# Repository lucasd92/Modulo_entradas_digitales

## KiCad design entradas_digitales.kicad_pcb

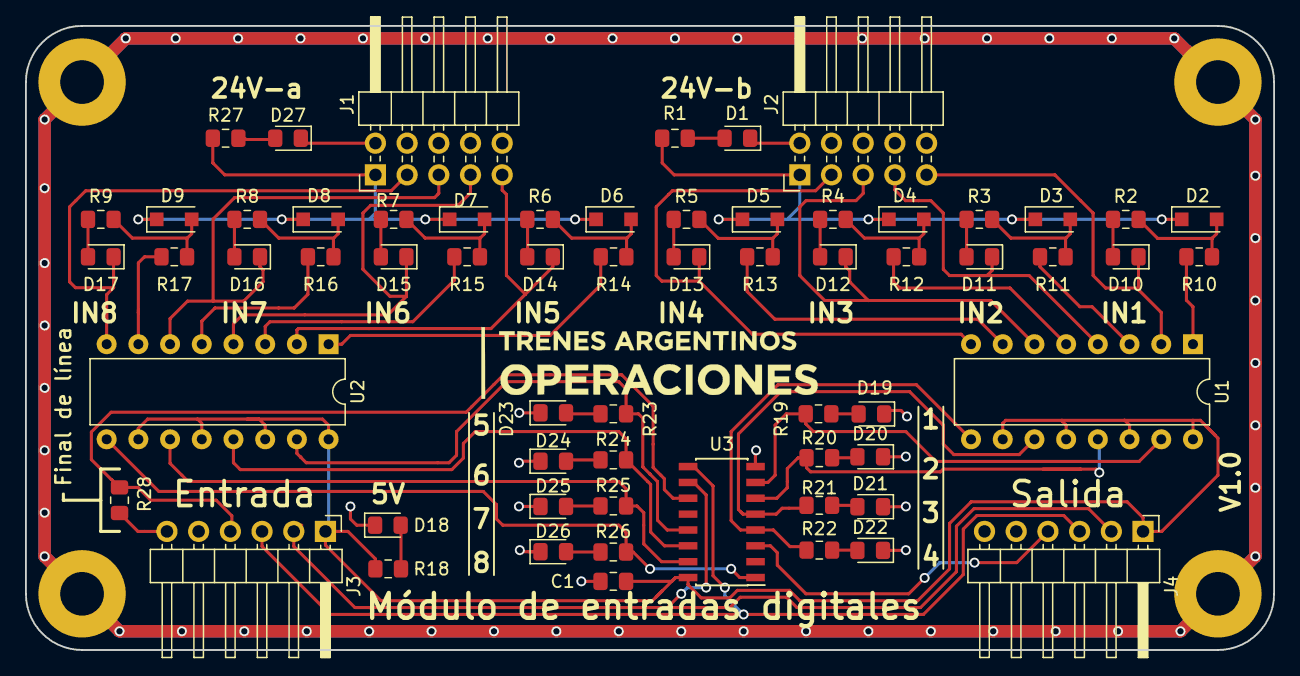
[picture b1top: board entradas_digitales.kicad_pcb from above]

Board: 2 copper layers, 100.0 x 50.0 mm, 68 parts (0 on the bottom side), 61 nets.

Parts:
C1: 100nF; C_0805_2012Metric_Pad1.15x1.40mm_HandSolder
D1, D10, D11, D12, D13, D14, D15, D16, D17, D18, D19, D20, D21, D22, D23, D24, D25, D26, D27: LED; LED_0805_2012Metric_Pad1.15x1.40mm_HandSolder
D2: KDZVTFTR12B; D_SOD-123F
D3, D4, D5, D6, D7, D8, D9: D_Zener; D_SOD-123F
G1: TrenesArgentinosLogo
J1: Opto5-8; PinHeader_2x05_P2.54mm_Horizontal
J2: Opto1-4; PinHeader_2x05_P2.54mm_Horizontal
J3: Entrada; PinHeader_1x06_P2.54mm_Horizontal
J4: Salida; PinHeader_1x06_P2.54mm_Horizontal
MH1, MH2, MH3, MH4: MountingHole_Pad; MountingHole_3.5mm_Pad
R1, R2, R3, R4, R5, R6, R7, R8, R9, R10, R11, R12, R13, R14, R15, R16, R17, R18, R19, R20, R21, R22, R23, R24, R25, R26, R27, R28: R; R_0805_2012Metric_Pad1.15x1.40mm_HandSolder
U1, U2: TLP627-4; DIP-16_W7.62mm
U3: 4021; SOIC-16_3.9x9.9mm_P1.27mm

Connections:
/1: R19.2, U1.15, U3.7
/2: R20.2, U1.13, U3.6
/3: R21.2, U1.11, U3.5
/4: R22.2, U1.9, U3.4
/5: R23.2, U2.15, U3.13
/6: R24.2, U2.13, U3.14
/7: R25.2, U2.11, U3.15
/8: R26.2, U2.9, U3.1
/24V-A: D2.1, D3.1, D4.1, D5.1, J2.1, R1.2
/24V-B: D6.1, D7.1, D8.1, D9.1, J1.1, R27.2
/CLK: J3.2, J4.2, U3.10
/GND-A: D1.1, J2.2
/GND-B: D27.1, J1.2
/IN1: D10.1, J2.9, U1.2
/IN2: D11.1, J2.7, U1.4
/IN3: D12.1, J2.5, U1.6
/IN4: D13.1, J2.3, U1.8
/IN5: D14.1, J1.9, U2.2
/IN6: D15.1, J1.7, U2.4
/IN7: D16.1, J1.5, U2.6
/IN8: D17.1, J1.3, U2.8
/PS: J3.3, J4.3, U3.9
/SIN: J3.4, R28.1, U3.11
/SOUT: J4.4, U3.3
unnamed: D1.2, R1.1
unnamed: D2.2, R2.1, R10.2
unnamed: D3.2, R3.1, R11.2
unnamed: D4.2, R4.1, R12.2
unnamed: D5.2, R5.1, R13.2
unnamed: D6.2, R6.1, R14.2
unnamed: D7.2, R7.1, R15.2
unnamed: D8.2, R8.1, R16.2
unnamed: D9.2, R9.1, R17.2
unnamed: D10.2, R2.2
unnamed: D11.2, R3.2
unnamed: D12.2, R4.2
unnamed: D13.2, R5.2
unnamed: D14.2, R6.2
unnamed: D15.2, R7.2
unnamed: D16.2, R8.2
unnamed: D17.2, R9.2
unnamed: D18.2, R18.1
unnamed: D19.2, R19.1
unnamed: D20.2, R20.1
unnamed: D21.2, R21.1
unnamed: D22.2, R22.1
unnamed: D23.2, R23.1
unnamed: D24.2, R24.1
unnamed: D25.2, R25.1
unnamed: D26.2, R26.1
unnamed: D27.2, R27.1
unnamed: R10.1, U1.1
unnamed: R11.1, U1.3
unnamed: R12.1, U1.5
unnamed: R13.1, U1.7
unnamed: R14.1, U2.1
unnamed: R15.1, U2.3
unnamed: R16.1, U2.5
unnamed: R17.1, U2.7
VDD: C1.1, J3.1, J4.1, R18.2, U1.10, U1.12, U1.14, U1.16, U2.10, U2.12, U2.14, U2.16, U3.16
VSS: C1.2, D18.1, D19.1, D20.1, D21.1, D22.1, D23.1, D24.1, D25.1, D26.1, J3.6, J4.6, MH1.1, MH2.1, MH3.1, MH4.1, R28.2, U3.8

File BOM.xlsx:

Eeschema (5.0.2)-1
Component Count: | 64
Ref | Qty | Value | Part | Footprint | Column1 | Datasheet | Description | Vendor
C1 | 1 | 100nF | C | Capacitor_SMD:C_0805_2012Metric_Pad1.15x1.40mm_HandSolder | 1276-1099-1-ND | https://www.digikey.com/product-detail/en/samsung-electro-me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 | Unpolarized capacitor
D1, D10, D11, D12 , D13, D14, D15, D16, D17, D27 | 10 | 17-21SURC/S530-A3/TR8 | LED | LED_SMD:LED_0805_2012Metric_Pad1.15x1.40mm_HandSolder |  | www.elemon.net | Light emitting diode
D2, D3, D4, D5, D6, D7, D8, D9 | 8 | MMSZ5242BTR | D_Zener | Diode_SMD:D_SOD-123F | 1655-1967-1-ND | https://www.digikey.com/product-detail/en/smc-diode-solution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 | Zener diode
D18, D19, D20, D21 , D22, D23, D24, D25 , D26 | 9 | 17-21SYGC/S530-E2/TR8 | LED | LED_SMD:LED_0805_2012Metric_Pad1.15x1.40mm_HandSolder |  | www.elemon.net | Light emitting diode
J1 | 1 | Opto5-8 | Conn_02x05_Odd_Even | Connector_PinHeader_2.54mm:PinHeader_2x05_P2.54mm_Horizontal |  | ~
J2 | 1 | Opto1-4 | Conn_02x05_Odd_Even | Connector_PinHeader_2.54mm:PinHeader_2x05_P2.54mm_Horizontal |  | ~
J3 | 1 | Entrada | Conn_01x06_Male | Connector_PinHeader_2.54mm:PinHeader_1x06_P2.54mm_Horizontal |  | ~
J4 | 1 | Salida | Conn_01x06_Male | Connector_PinHeader_2.54mm:PinHeader_1x06_P2.54mm_Horizontal |  | ~
R1, R2, R3, R4, R5, R6, R7, R8, R9, R10 , R11, R12, R13, R14 , R15, R16, R17, R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 | 19 | 10K | R | Resistor_SMD:R_0805_2012Metric_Pad1.15x1.40mm_HandSolder | 2019-RK73B2ATTD103JCT-ND | https://www.digikey.com/product-detail/en/koa-speer-electron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 | Resistor
R18, R19, R20, R21 , R22, R23, R24, R25 , R26 | 9 | 2K2 | R | Resistor_SMD:R_0805_2012Metric_Pad1.15x1.40mm_HandSolder | RMCF0805JT2K20CT-ND | https://www.digikey.com/product-detail/en/stackpole-electron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 | Resistor
U1, U2 | 2 | LTV-845 | TLP627-4 | Package_DIP:DIP-16_W7.62mm | 160-2041-5-ND | https://www.digikey.com/product-detail/en/lite-on-inc/LTV-84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 | DC Quad Darlington Optocoupler, Vce 300V, CTR 1000%, DIP16
U3 | 1 | 4021 | 4021 | Package_SO:SOIC-16_3.9x9.9mm_P1.27mm | 296-38905-1-ND | https://www.digikey.com/product-detail/en/texas-instruments/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 | CD4021
 | 1 |  |  |  | TS391AX10-ND | https://www.digikey.com/product-detail/en/chip-quik-inc/TS39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

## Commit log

2019-08-06 Creación del repositorio
    Agregado de todos los archivos del diseño.
2019-08-07 Agregado de BOM
2019-08-15 BOM actualizada
    Se adaptó la BOM a un formato que pueda leer digikey,
